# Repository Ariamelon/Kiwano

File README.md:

# Kiwano
Ring rotary encoder and PMW3360/Cirque [VIK](https://github.com/sadekbaroudi/vik) module with RGB backlight.

## Disclaimer
This board is licensed under CERN-OHL-S-2.0.

## Key Features
* PER56 rotary ring encoder.
* Illuminated RGB ring.
* Cirque trackpad support in the middle of the PER56.
* PMW3360 and 34mm trackball support in the middle of the PER56, utilizing 7.5mm BTUs (e.g. Veichu VCN310 7.5mm).
* Trackball has two styles: illuminated outer ring, and illuminated trackball.

## VIK module certification card

| Category                | Classification          | Response           |
| ----------------------- | ----------------------- | ------------------ |
| FPC connector           | Required                | :heavy_check_mark: |
| Breakout pins           | Recommended             | :x:                |
| Uses: SPI               | Optional                | :heavy_check_mark: |
| SPI used for SPI only   | Strongly recommended    | :heavy_check_mark: |
| Uses: I2C               | Optional                | :heavy_check_mark: |
| I2C used for I2C only   | Strongly Recommended    | :heavy_check_mark: |
| I2C pull ups            | Required                | :heavy_check_mark: |
| Uses: RGB               | Optional                | :heavy_check_mark: |
| Uses: Extra GPIO 1      | Optional                | :heavy_check_mark: |
| Uses: Extra GPIO 2      | Optional                | :heavy_check_mark: |
| Standard PCB Size/Mount | Strongly Recommended    | Large              |

## Changelog
* 22/10/2024: CERN-OHL-S-2.0 license added.
* 14/10/2023: V1.1 update. Changed LDO to XC6206P202MR. Removed RC filter and pullup from encoder pins.
* 18/09/2023: Fixed .gitignore file. Increased tolerances of PER-56 base mount.
* 28/08/2023: Unified component libraries into one big library. Fixed 3DP files.
* 04/08/2023: Updated SK6812 MINI-E and switch footprints. Changed VIK FFC to FH12. Stitched ground planes together. Fixed VIK footprint. Moved production files to easier to access location.
* 02/08/2023: Fixed 3DP files.
* 01/08/2023: Files for trackpad mount and knob moved here from [Honeydew](https://github.com/Ariamelon/Honeydew/). Added trackball mount STEP files, using 7.5mm BTUs.
* 30/07/2023: Updated BOM.
* 29/07/2023: Added VIK size row to certification card.
* 28/07/2023: Initial commit.

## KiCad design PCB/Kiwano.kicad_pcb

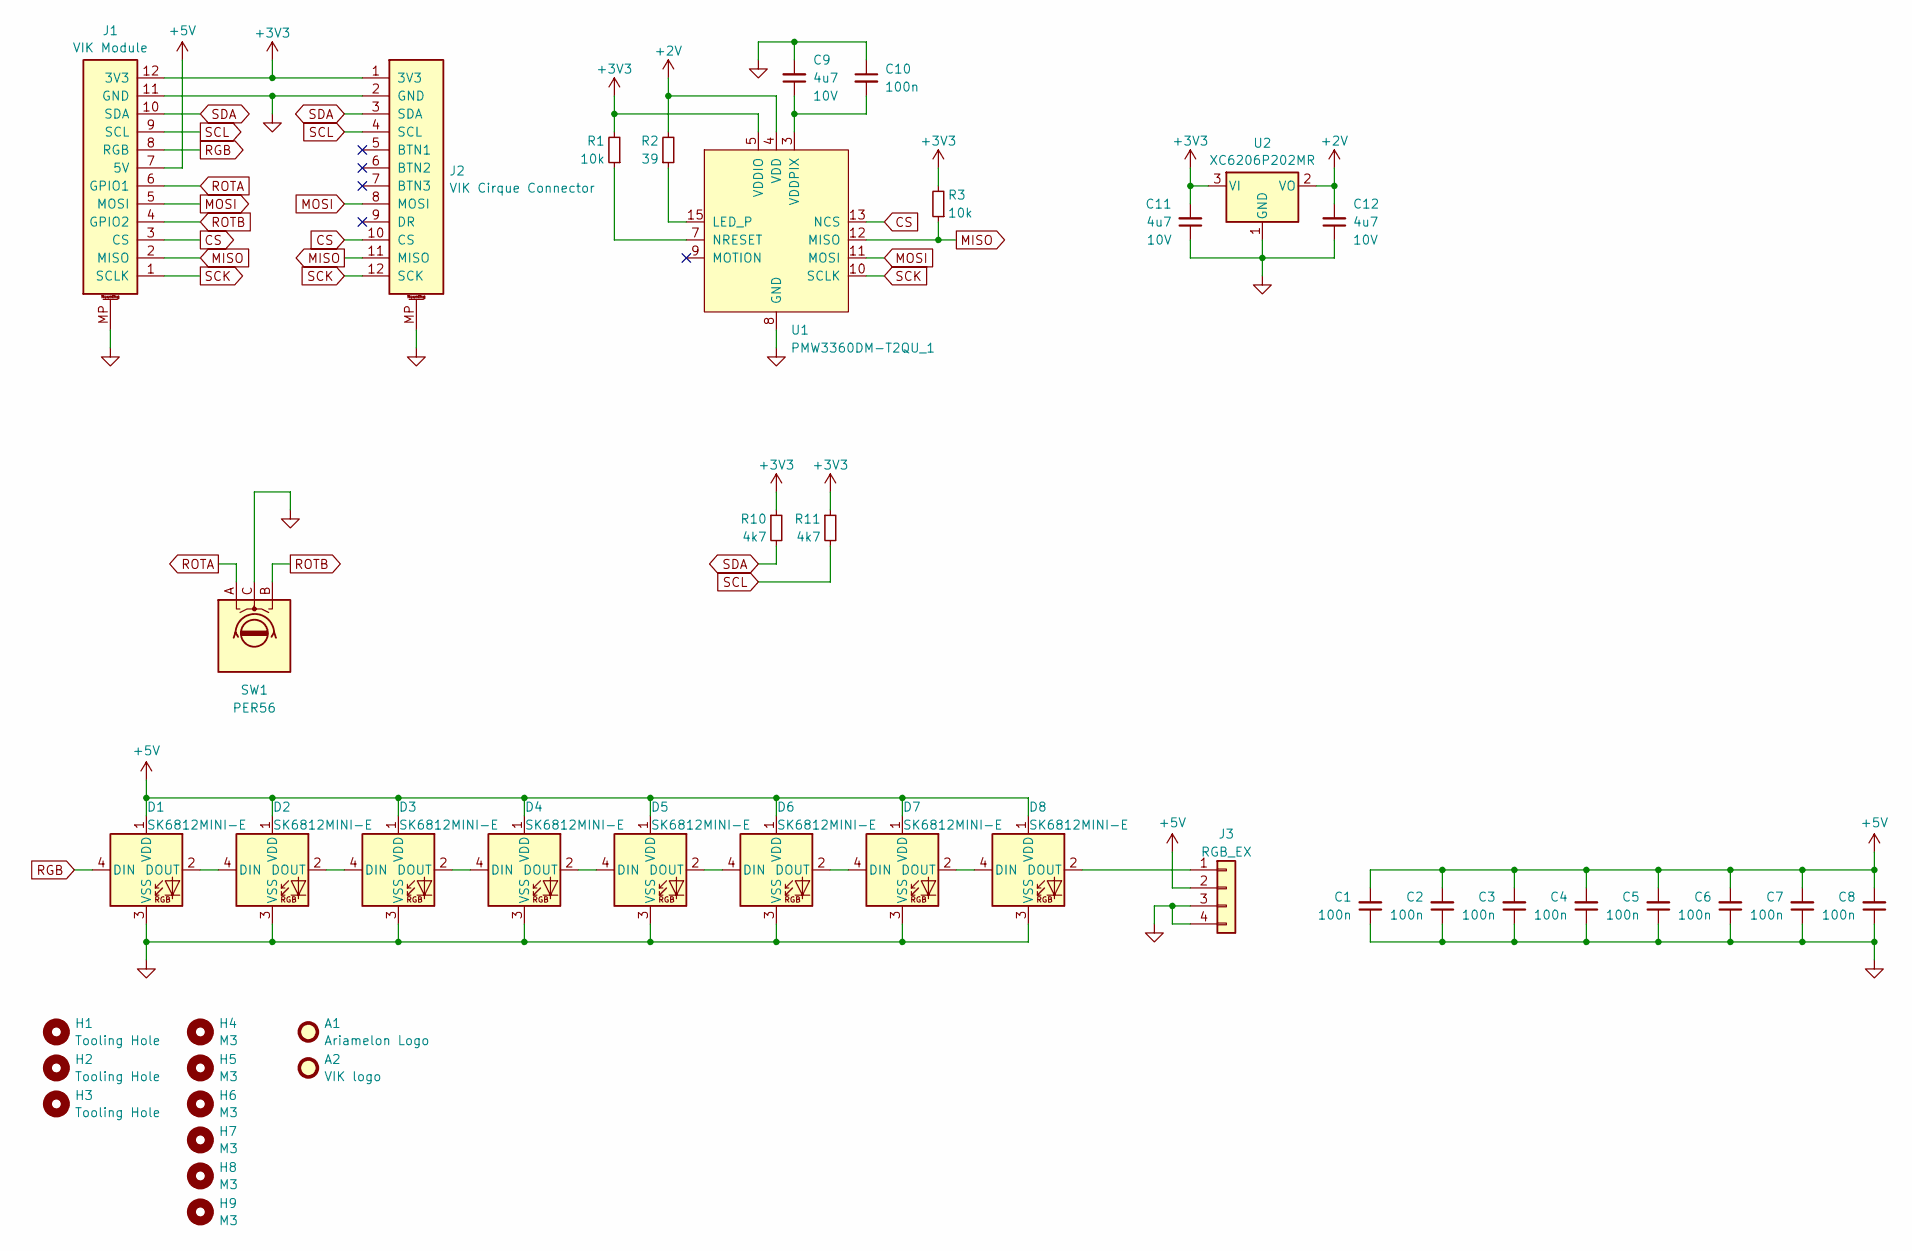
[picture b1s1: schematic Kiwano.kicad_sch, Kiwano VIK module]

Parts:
A1: Ariamelon Logo; Ariamelon_Logo_Small_Mask
A2: VIK logo; VIK_Logo_Small
C1, C2, C3, C4, C5, C6, C7, C8, C10: 100n; C_0402_1005Metric; Voltage 50V; LCSC C307331
C9, C11, C12: 4u7; C_0402_1005Metric; Voltage 10V; LCSC C23733
D1, D2, D3, D4, D5, D6, D7, D8: SK6812MINI-E; LED_OPSCO_SK6812MINI-E; LCSC C524051
H1, H2, H3: Tooling Hole; MountingHole_JLC-Tooling
H4, H5, H6, H7, H8, H9: M3; MountingHole_3.2mm_M3_Pad
J1: VIK Module; VIK_Module_Horizontal; LCSC C88360
J2: VIK Cirque Connector; VIK_Cirque_Horizontal; LCSC C88360
J3: RGB_EX; PinHeader_RGB
R1, R3: 10k; R_0402_1005Metric; LCSC C25744
R2: 39; R_0402_1005Metric; LCSC C25164
R10, R11: 4k7; R_0402_1005Metric; LCSC C25900
SW1: PER56; RotaryEncoder_Bourns_PER561-P115-N0015; LCSC C470483
U1: PMW3360DM-T2QU_1; PixArt_PMW3360DM-T2QU
U2: XC6206P202MR; SOT-23-3; LCSC C2891260

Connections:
+2V: C12.2, R2.2, U1.4 (VDD), U2.2 (VO)
+3V3: C11.2, J1.12 (3V3), J2.1 (3V3), R1.2, R3.2, R10.1, R11.1, U1.5 (VDDIO), U2.3 (VI)
+5V: C1.2, C2.2, C3.2, C4.2, C5.2, C6.2, C7.2, C8.2, D1.1 (VDD), D2.1 (VDD), D3.1 (VDD), D4.1 (VDD), D5.1 (VDD), D6.1 (VDD), D7.1 (VDD), D8.1 (VDD), J1.7 (5V), J3.2
CS: J1.3 (CS), J2.10 (CS), U1.13 (NCS)
GND: C1.1, C2.1, C3.1, C4.1, C5.1, C6.1, C7.1, C8.1, C9.2, C10.1, C11.1, C12.1, D1.3 (VSS), D2.3 (VSS), D3.3 (VSS), D4.3 (VSS), D5.3 (VSS), D6.3 (VSS), D7.3 (VSS), D8.3 (VSS), J1.11 (GND), J1.MP, J2.2 (GND), J2.MP, J3.3, J3.4, SW1.C, U1.8 (GND), U2.1 (GND)
MISO: J1.2 (MISO), J2.11 (MISO), R3.1, U1.12 (MISO)
MOSI: J1.5 (MOSI), J2.8 (MOSI), U1.11 (MOSI)
unnamed: D1.2 (DOUT), D2.4 (DIN)
unnamed: D2.2 (DOUT), D3.4 (DIN)
unnamed: D3.2 (DOUT), D4.4 (DIN)
unnamed: D4.2 (DOUT), D5.4 (DIN)
unnamed: D5.2 (DOUT), D6.4 (DIN)
unnamed: D6.2 (DOUT), D7.4 (DIN)
unnamed: D7.2 (DOUT), D8.4 (DIN)
unnamed: D8.2 (DOUT), J3.1
unnamed: R2.1, U1.15 (LED_P)
unnamed: R1.1, U1.7 (NRESET)
unnamed: C9.1, C10.2, U1.3 (VDDPIX)
RGB: D1.4 (DIN), J1.8 (RGB)
ROTA: J1.6 (GPIO1), SW1.A
ROTB: J1.4 (GPIO2), SW1.B
SCK: J1.1 (SCLK), J2.12 (SCK), U1.10 (SCLK)
SCL: J1.9 (SCL), J2.4 (SCL), R11.2
SDA: J1.10 (SDA), J2.3 (SDA), R10.2

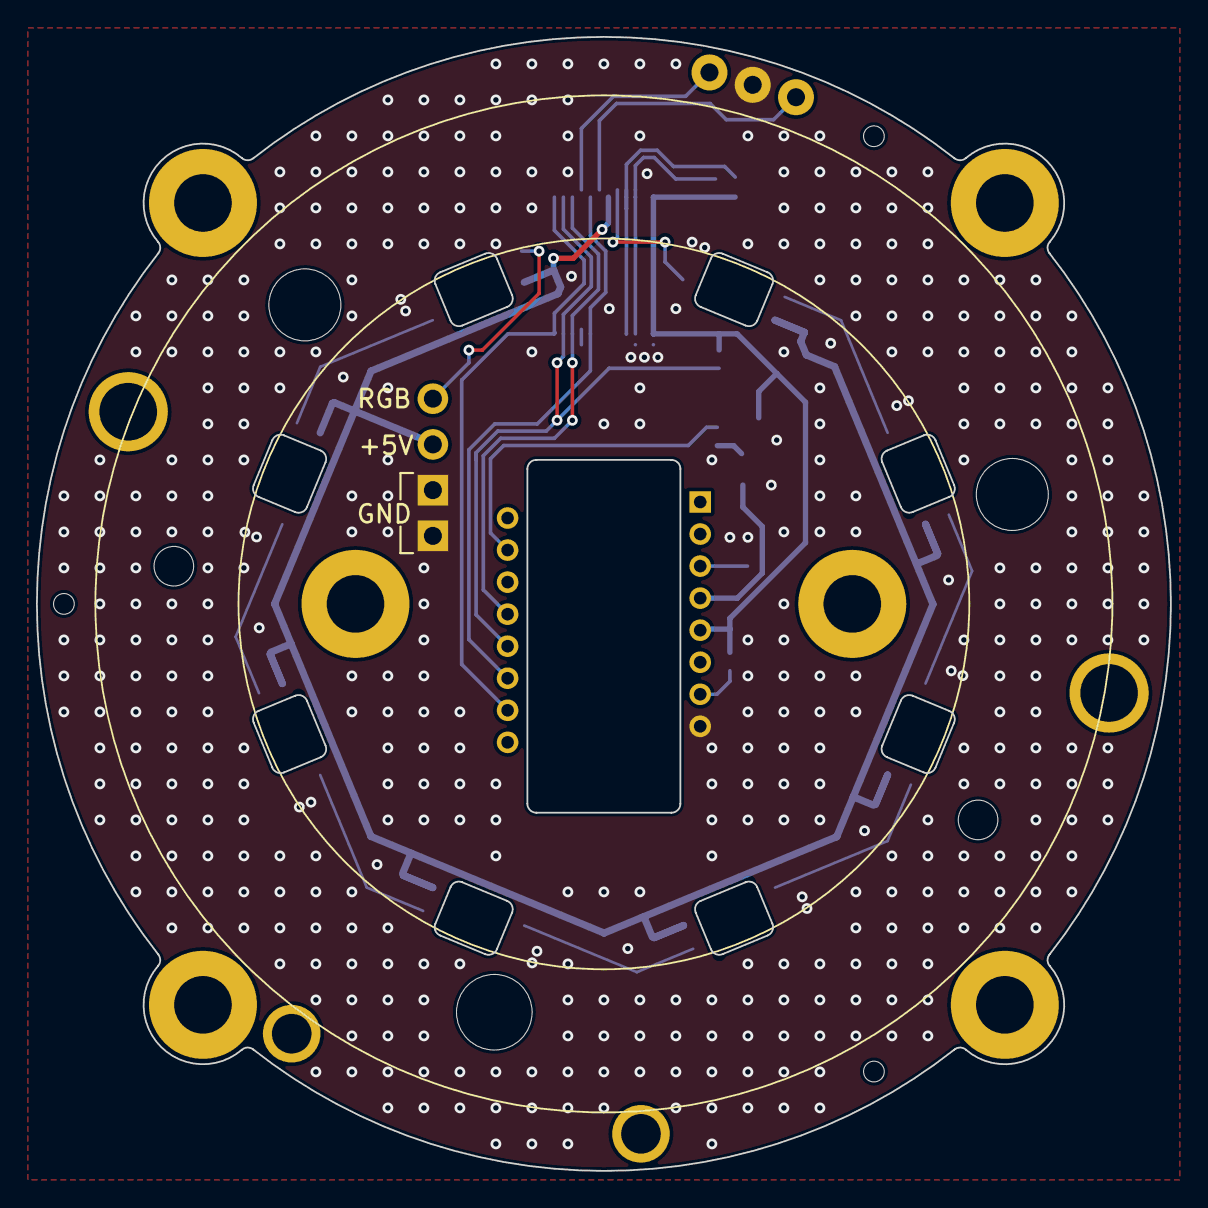
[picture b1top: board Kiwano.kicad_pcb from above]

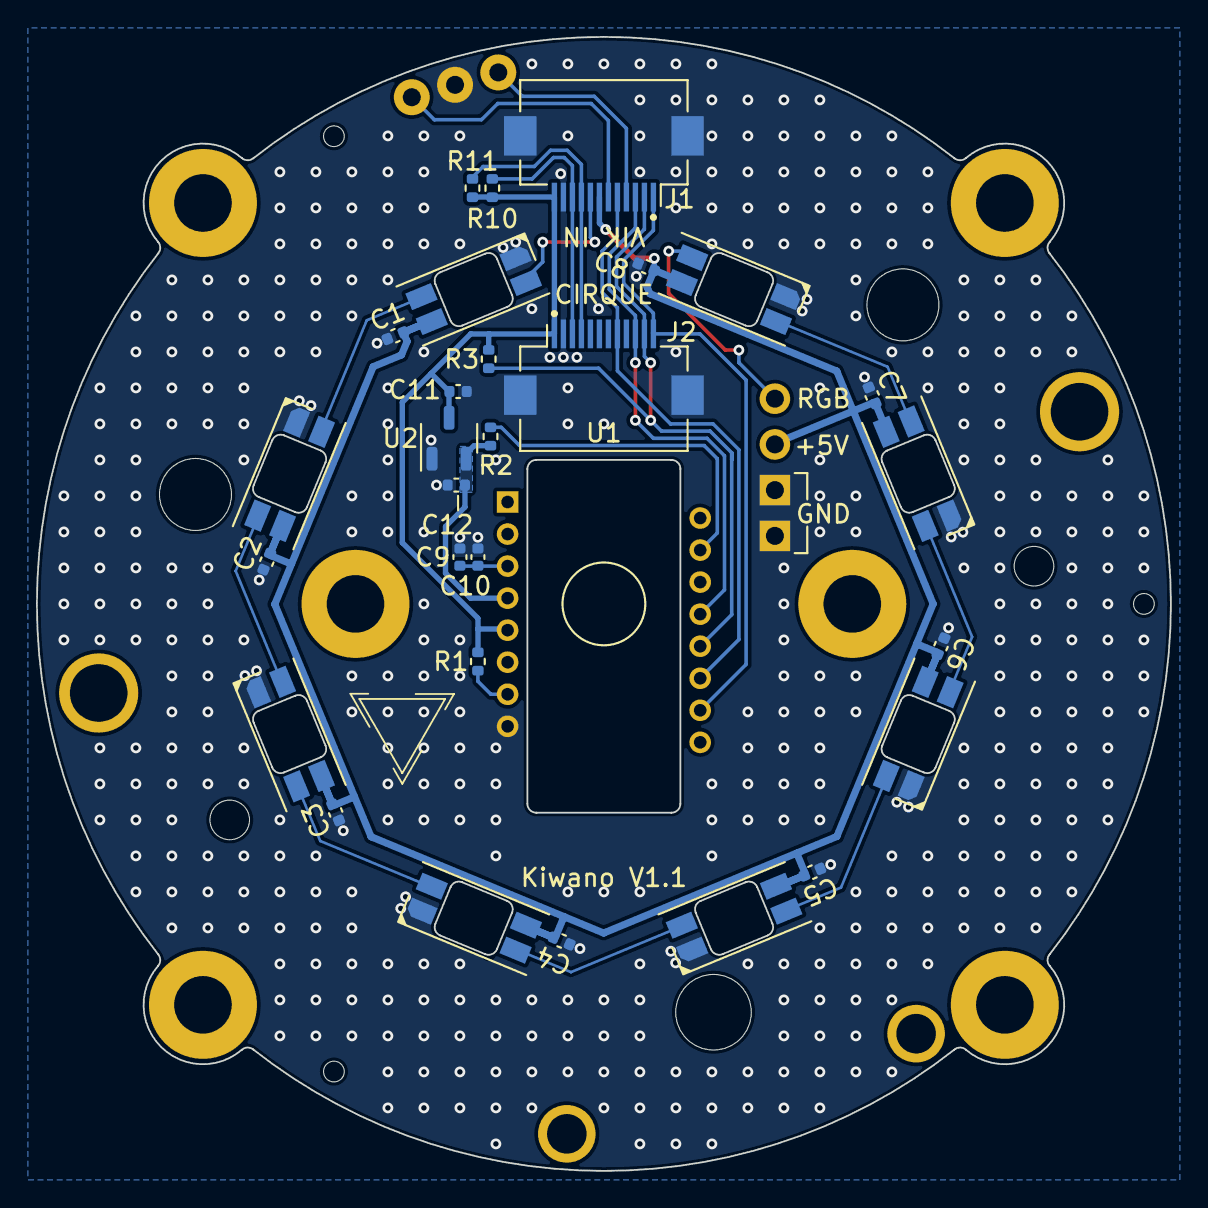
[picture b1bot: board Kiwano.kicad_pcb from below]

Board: 2 copper layers, 63.0 x 63.0 mm, 42 parts (33 on the bottom side), 24 nets.

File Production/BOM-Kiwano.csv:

Comment,Designator,Footprint,LCSC
4u7,"C11,C12,C9",C_0402_1005Metric,C23733
39,R2,R_0402_1005Metric,C25164
10k,"R1,R3",R_0402_1005Metric,C25744
4k7,"R10,R11",R_0402_1005Metric,C25900
 XC6206P202MR,U2,SOT-23-3,C2891260
100n,"C1,C10,C2,C3,C4,C5,C6,C7,C8",C_0402_1005Metric,C307331
PER56,SW1,RotaryEncoder_Bourns_PER561-P115-N0015,C470483
SK6812MINI-E,"D1,D2,D3,D4,D5,D6,D7,D8",LED_OPSCO_SK6812MINI-E,C524051
VIK Module,"J1,J2",VIK_Module_Horizontal,C88360
PMW3360DM-T2QU_1,U1,PixArt_PMW3360DM-T2QU,

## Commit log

2023-07-28 Added VIK size row to certification card.
2023-07-30 30/07/2023 update
    Updated BOM.
2023-08-01 Fixed silk, moved production files.
2023-08-01 01/08/2023 update
    Files for trackpad mount and knob moved here from Honeydew. Added trackball mount STEP files, using 7.5mm BTUs.
2023-08-02 02/08/2023 update
    Fixed 3DP files.
2023-08-04 04/08/2023 update
    Updated SK6812 MINI-E and switch footprints. Changed VIK FFC to FH12. Stitched ground planes together. Fixed VIK footprint. Moved production files to easier to access location.
2023-08-28 28/08/2023 update
    Unified component libraries into one big library. Fixed 3DP files.
2023-09-18 18/09/2023 update
    Fixed .gitignore file.
2023-09-18 18/09/2023 update
    Fixed .gitignore file. Increased tolerances of PER-56 base mount.
2023-10-14 V1.1 update
    Changed LDO to XC6206P202MR. Removed RC filter and pullup from encoder pins.
2024-10-22 License updated to CERN-OHL-S-2.0.

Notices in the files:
PCB/Kiwano.kicad_pcb:
Licensed under CC BY 4.0.
